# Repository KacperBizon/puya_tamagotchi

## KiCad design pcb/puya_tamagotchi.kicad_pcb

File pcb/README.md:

* PA0 - RED DIODE
* PA1 - WHITE DIODE
* PA2 - SWCLK
* PA3 - LDR_DRIVE
* PA4 - BUTTON_1
* PA5 - BUTTON_2
* PA6 - BUTTON_3
* PA7 - BUTTON_4

* PB0 - TIM1_CH2 - BUZZER
* PB1 - ADC_IN0 - LDR_OUT
* PB3 - I2C1 SDL - SSD1306
* PB4 - I2C1 SDA - SSD1306
* PB6 - SWDIO
* PB7 - NC

* PC1 - NC

* TP1 - GND
* TP2 - VCC
* TP3 - VBUS
* TP4 - +BATT
* TP5 - I2C.SCL
* TP6 - I2C.SDA

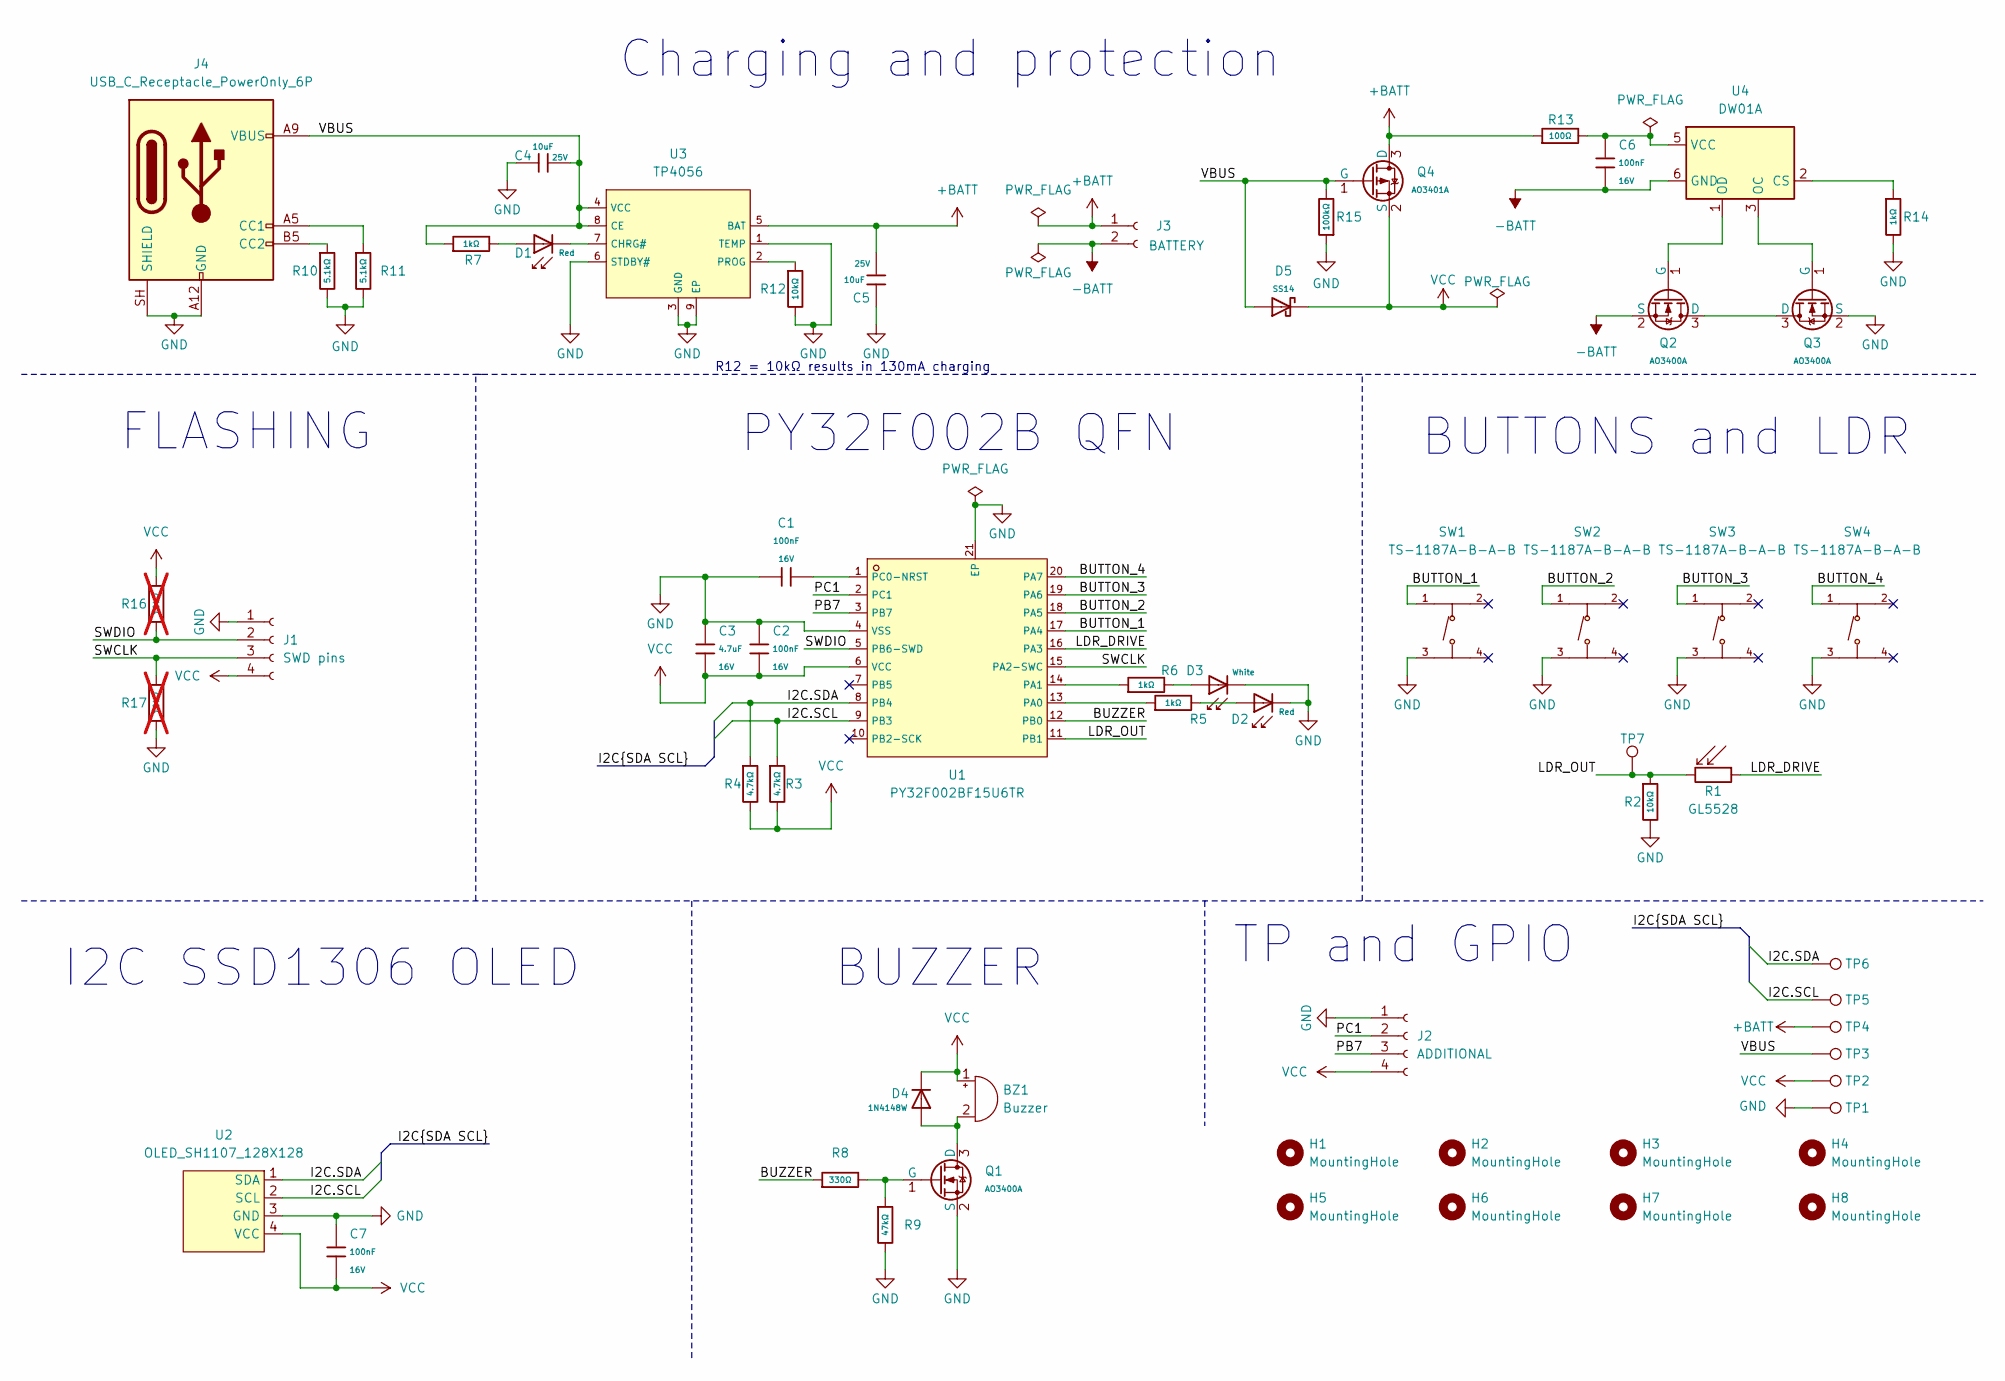
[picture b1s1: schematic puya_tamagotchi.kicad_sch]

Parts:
BZ1: Buzzer; Buzzer_12x9.5RM7.6
C1, C2, C6, C7: 100nF; C_0402; Voltage Rated 16V; Tolerance ±10%; Part CL05B104KO5NNNC; LCSC C1525
C3: 4.7uF; C_0603; Voltage Rated 16V; Tolerance ±10%; Part CL10A475KO8NNNC; LCSC C19666
C4, C5: 10uF; C_0603; Voltage Rated 25V; Tolerance ±20%; Part CL10A106MA8NRNC; LCSC C96446
D1, D2: Red; D_0603; Part KT-0603R; LCSC C2286
D3: White; D_0603; Part KT-0603W; LCSC C2290
D4: 1N4148W; D_SOD-123; Forward Voltage (Vf@If) 1V@50mA; Reverse Voltage (Vr) 75V; Part 1N4148W; LCSC C81598
D5: SS14; D_SMA; Forward Voltage (Vf@If) 550mV@1A; Reverse Voltage (Vr) 40V; Part SS14; LCSC C2480
H1, H2, H3, H4, H5, H6, H7, H8: MountingHole; MountingHole_2.2mm_M2
J1: SWD pins; PinSocket_1x04_P2.54mm_Vertical
J2: ADDITIONAL; PinSocket_1x04_P2.54mm_Vertical
J3: BATTERY; JST_EH_B2B-EH-A_1x02_P2.50mm_Vertical
J4: USB_C_Receptacle_PowerOnly_6P; USB_C_Receptacle_HRO_TYPE-C-31-M-17
Q1, Q2, Q3: AO3400A; Q_SOT-23; Part AO3400A; LCSC C20917
Q4: AO3401A; Q_SOT-23; Part AO3401A; LCSC C15127
R1: GL5528; R_LDR_5.1x4.3mm_P3.4mm_Vertical
R2, R12: 10kΩ; R_0402; Overload Voltage (Max) 50V; Tolerance ±1%; Part 0402WGF1002TCE; LCSC C25744
R3, R4: 4.7kΩ; R_0402; Overload Voltage (Max) 50V; Tolerance ±1%; Part 0402WGF4701TCE; LCSC C25900
R5, R6, R7, R14: 1kΩ; R_0402; Overload Voltage (Max) 50V; Tolerance ±1%; Part 0402WGF1001TCE; LCSC C11702
R8: 330Ω; R_0402; Overload Voltage (Max) 50V; Tolerance ±1%; Part 0402WGF3300TCE; LCSC C25104
R9: 47kΩ; R_0402; Overload Voltage (Max) 50V; Tolerance ±1%; Part 0402WGF4702TCE; LCSC C25792
R10, R11: 5.1kΩ; R_0402; Overload Voltage (Max) 50V; Tolerance ±1%; Part 0402WGF5101TCE; LCSC C25905
R13: 100Ω; R_0402; Overload Voltage (Max) 50V; Tolerance ±1%; Part 0402WGF1000TCE; LCSC C25076
R15: 100kΩ; R_0402; Overload Voltage (Max) 50V; Tolerance ±1%; Part 0402WGF1003TCE; LCSC C25741
R16, R17: 10kΩ; R_0402; Overload Voltage (Max) 50V; Tolerance ±1%; Part 0402WGF1002TCE; LCSC C25744; not fitted
SW1, SW2, SW3, SW4: TS-1187A-B-A-B; SW-SMD_4P-L5.1-W5.1-P3.70-LS6.5-TL_H1.5; LCSC C318884
TP1, TP2, TP3, TP4, TP5, TP6, TP7: TestPoint; TestPoint_Pad_D1.0mm
U1: PY32F002BF15U6TR; QFN-20_L3.0-W3.0-P0.40-TL-EP1.7; LCSC C7469099
U2: OLED_SH1107_128X128; SH1107_128x128_OLED
U3: TP4056; ESOP-8_L4.9-W3.9-P1.27-LS6.0-BL-EP; Part TP4056-42-ESOP8; LCSC C16581
U4: DW01A; SOT-23-6

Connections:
+BATT: C5.2, J3.1, Q4.3 (D), R13.1, TP4.1 (1_1), U3.5 (BAT)
-BATT: C6.2, J3.2, Q2.2 (S), U4.6 (GND)
/BUTTON_1: SW1.1 (A), U1.17 (PA4)
/BUTTON_2: SW2.1 (A), U1.18 (PA5)
/BUTTON_3: SW3.1 (A), U1.19 (PA6)
/BUTTON_4: SW4.1 (A), U1.20 (PA7)
/BUZZER: R8.1, U1.12 (PB0)
/I2C.SCL: R3.1, TP5.1 (1_1), U1.9 (PB3), U2.2 (SCL)
/I2C.SDA: R4.1, TP6.1 (1_1), U1.8 (PB4), U2.1 (SDA)
/LDR_DRIVE: R1.1, U1.16 (PA3)
/LDR_OUT: R1.2, R2.1, TP7.1 (1_1), U1.11 (PB1)
/PB7: J2.3, U1.3 (PB7)
/PC1: J2.2, U1.2 (PC1)
/SWCLK: J1.3, R17.1, U1.15 (PA2-SWC)
/SWDIO: J1.2, R16.2, U1.5 (PB6-SWD)
/VBUS: C4.2, D5.2, J4.A9 (VBUS), J4.B9 (VBUS), Q4.1 (G), R7.1, R15.2, TP3.1 (1_1), U3.4 (VCC), U3.8 (CE)
GND: C1.1, C2.1, C3.1, C4.1, C5.1, C7.1, D2.1, D3.1, J1.1, J2.1, J4.A12 (GND), J4.B12 (GND), J4.SH (SHIELD), Q1.2 (S), Q3.2 (S), R2.2, R9.2, R10.2, R11.2, R12.2, R14.2, R15.1, R17.2, SW1.3 (C), SW2.3 (C), SW3.3 (C), SW4.3 (C), TP1.1 (1_1), U1.4 (VSS), U1.21 (EP), U2.3 (GND), U3.1 (TEMP), U3.3 (GND), U3.6 (STDBY#), U3.9 (EP)
unnamed: BZ1.2 (-), D4.2, Q1.3 (D)
unnamed: D1.2, R7.2
unnamed: D2.2, R5.2
unnamed: D3.2, R6.2
unnamed: J4.A5 (CC1), R11.1
unnamed: J4.B5 (CC2), R10.1
unnamed: Q1.1 (G), R8.2, R9.1
unnamed: Q2.3 (D), Q3.3 (D)
unnamed: Q2.1 (G), U4.1 (OD)
unnamed: Q3.1 (G), U4.3 (OC)
unnamed: R5.1, U1.13 (PA0)
unnamed: R6.1, U1.14 (PA1)
unnamed: C1.2, U1.1 (PC0-NRST)
unnamed: D1.1, U3.7 (CHRG#)
unnamed: R12.1, U3.2 (PROG)
unnamed: R14.1, U4.2 (CS)
unnamed: C6.1, R13.2, U4.5 (VCC)
VCC: BZ1.1 (+), C2.2, C3.2, C7.2, D4.1, D5.1, J1.4, J2.4, Q4.2 (S), R3.2, R4.2, R16.1, TP2.1 (1_1), U1.6 (VCC), U2.4 (VCC)

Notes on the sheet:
Charging and protection
R12 = 10kΩ results in 130mA charging
BUTTONS and LDR
BUZZER
PY32F002B QFN
FLASHING
TP and GPIO
I2C SSD1306 OLED

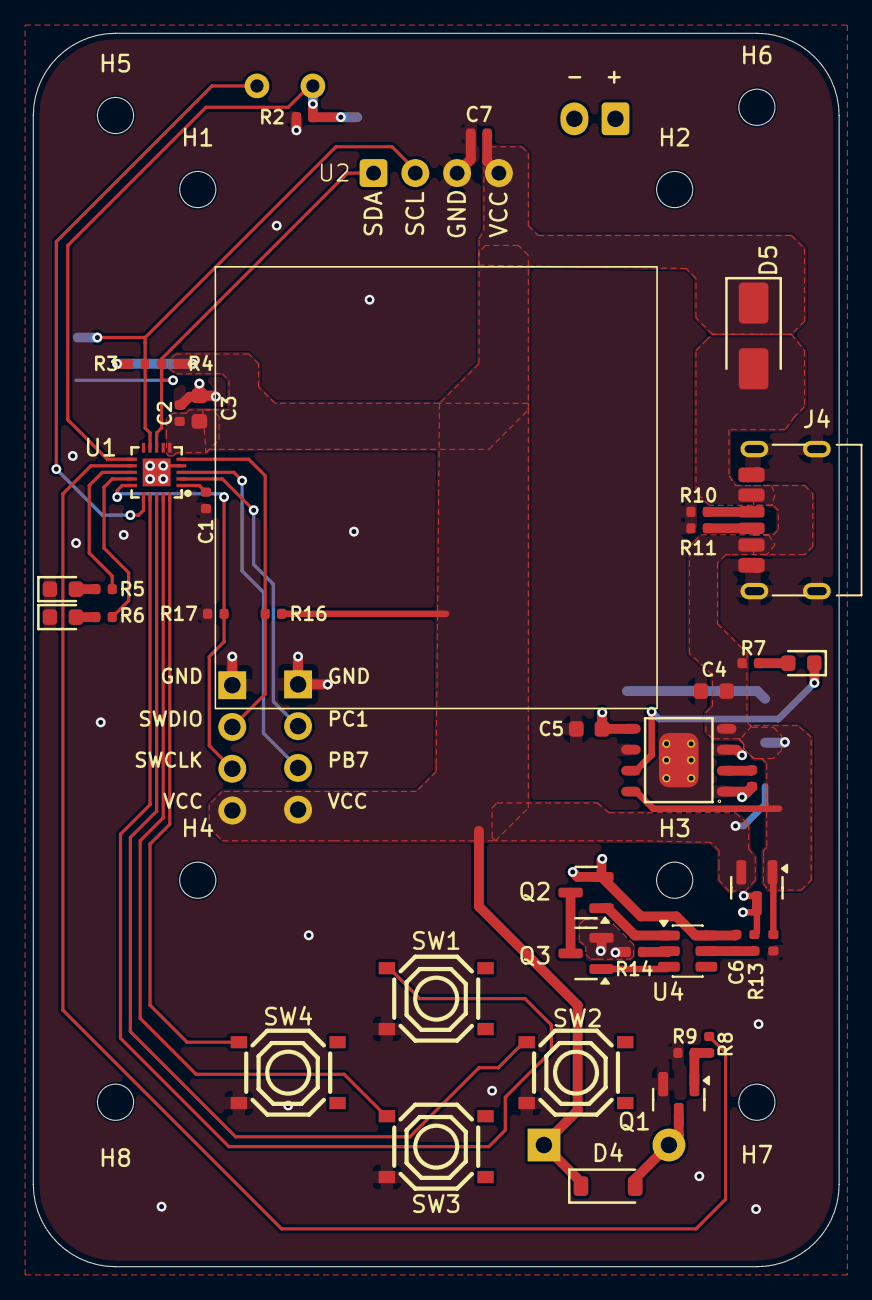
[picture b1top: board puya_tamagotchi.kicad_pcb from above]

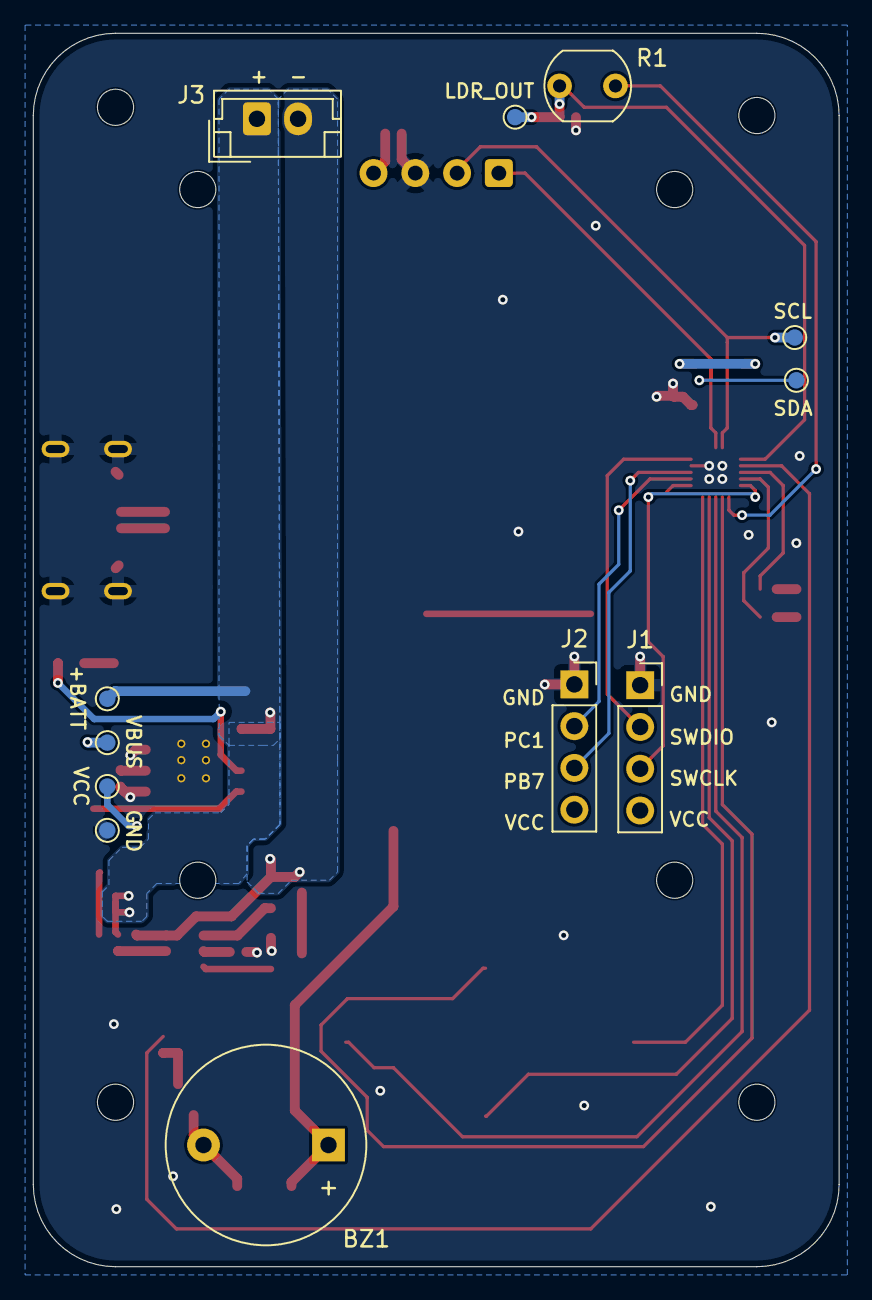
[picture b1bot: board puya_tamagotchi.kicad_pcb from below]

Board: 2 copper layers, 49.0 x 75.0 mm, 61 parts (12 on the bottom side), 35 nets.
